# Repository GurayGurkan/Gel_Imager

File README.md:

# Open Science Multi-function Gel Imager
*An Open-Hardware Agorose Gel and Chemiluminicance Imaging System Based on Raspberry Pi 4B*

This repository involves:
  - **Mechanical Design Files**: FreeCAD drawingshousing of Incu-stream mechanical parts
  - **Electronics**: Circuit schematics and PCB layout files of Raspberrry Pi 4B shield and led control electronics.
  - **Software**: Involves Python codes for main control and user interface. 
  -

For suggestions and questions, please e-mail to ***guraygurkan@istanbul.edu.tr***

Cheers!

Guray Gurkan

* **Please cite this repo as:** 

(Under Review: submitted to Scientific Reports for review)

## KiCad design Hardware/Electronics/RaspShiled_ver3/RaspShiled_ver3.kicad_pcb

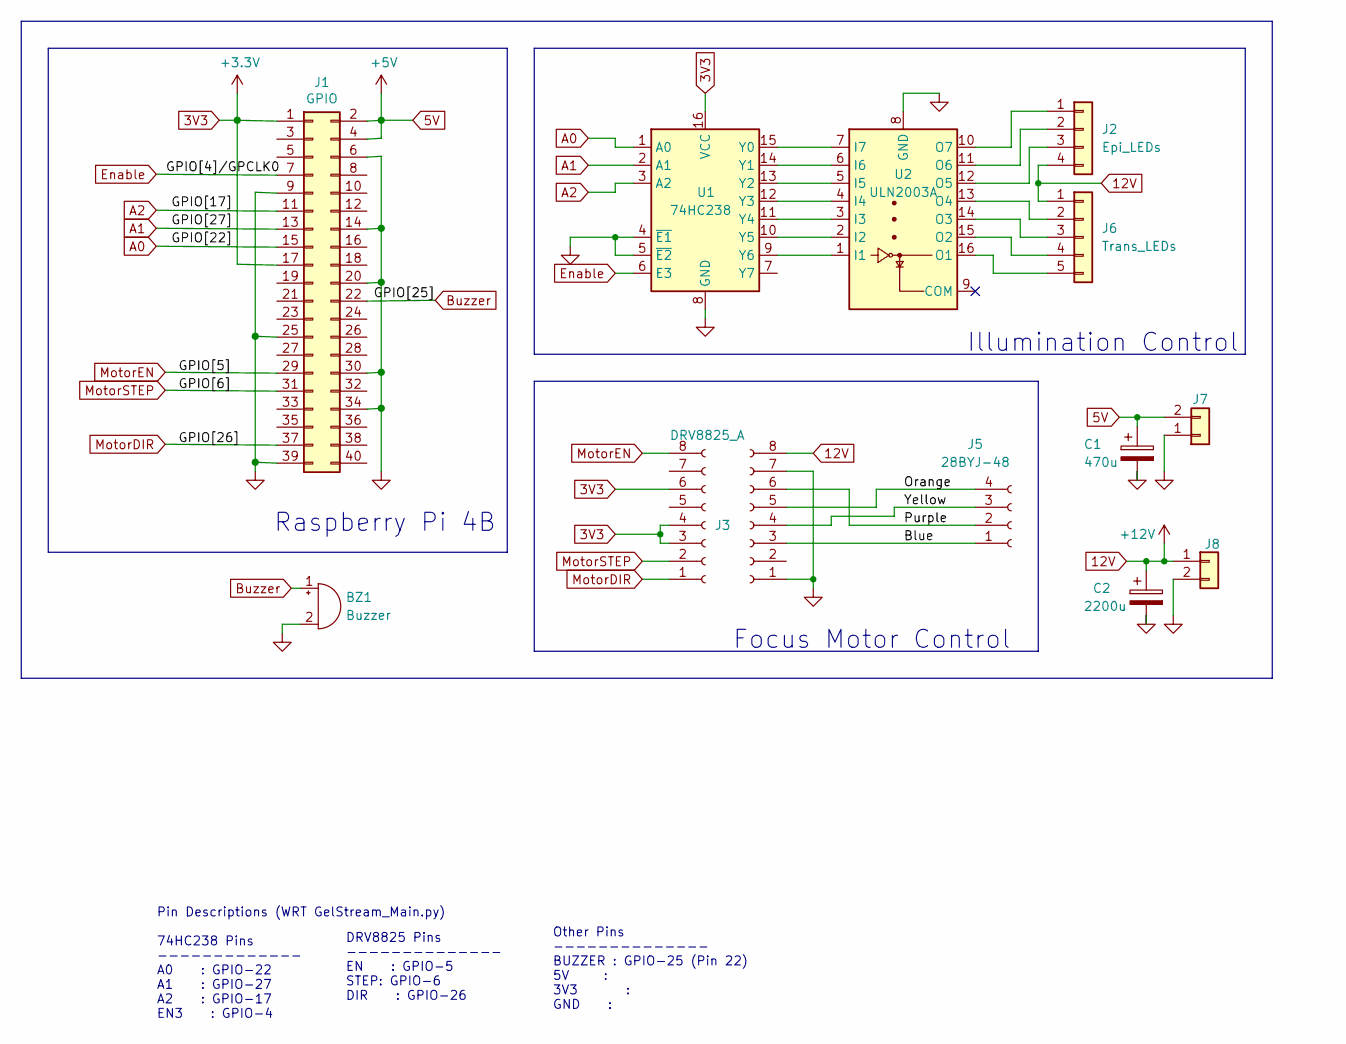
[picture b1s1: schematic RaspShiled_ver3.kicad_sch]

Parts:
BZ1: Buzzer; Buzzer_12x9.5RM7.6
C1: 470u; CP_Radial_D6.3mm_P2.50mm
C2: 2200u; CP_Radial_D6.3mm_P2.50mm
J1: GPIO; PinHeader_2x20_P2.54mm_Vertical
J2: Epi_LEDs; PinHeader_1x04_P2.54mm_Vertical
J3: DRV8825_A; PinSocket_1x08_P2.54mm_Vertical
J4: DRV8825_B; PinSocket_1x08_P2.54mm_Vertical
J5: 28BYJ-48; PinHeader_1x05_P2.54mm_Vertical
J6: Trans_LEDs; PinHeader_1x05_P2.54mm_Vertical
J7, J8: Conn_01x02; TerminalBlock_MetzConnect_Type011_RT05502HBWC_1x02_P5.00mm_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
U1: 74HC238; SOIC-16_3.9x9.9mm_P1.27mm
U2: ULN2003A; DIP-16_W7.62mm

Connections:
3V3: J1.1, J1.17, J3.3, J3.4, J3.6, U1.16 (VCC)
5V: C1.1, J1.2, J1.4, J7.2
12V: C2.1, J2.4, J4.8, J6.1, J8.1
/Blue: J4.3, J5.1
/GPIO[2]/SDA1: J1.3
/GPIO[3]/SCL1: J1.5
/GPIO[7]/SPI0.CE1: J1.26
/GPIO[8]/SPI0.CE0: J1.24
/GPIO[9]/SPI0.MISO: J1.21
/GPIO[10]/SPI0.MOSI: J1.19
/GPIO[11]/SPI0.SCLK: J1.23
/GPIO[12]/PWM0: J1.32
/GPIO[13]/PWM1: J1.33
/GPIO[14]/TXD0: J1.8
/GPIO[15]/RXD0: J1.10
/GPIO[16]: J1.36
/GPIO[18]/PCM.CLK: J1.12
/GPIO[19]/PCM.FS: J1.35
/GPIO[20]/PCM.DIN: J1.38
/GPIO[21]/PCM.DOUT: J1.40
/GPIO[23]: J1.16
/ID_SCL: J1.28
/ID_SDA: J1.27
/Orange: J4.5, J5.4
/Purple: J4.6, J5.2
/Yellow: J4.4, J5.3
A0: J1.15, U1.1 (A0)
A1: J1.13, U1.2 (A1)
A2: J1.11, U1.3 (A2)
Buzzer: BZ1.1 (-), J1.22
Enable: J1.7, U1.6 (E3)
Epi_Blue_EN: U1.15 (Y0), U2.7 (I7)
Epi_Green_EN: U1.13 (Y2), U2.5 (I5)
Epi_Red_EN: U1.14 (Y1), U2.6 (I6)
GND: BZ1.2 (+), C1.2, C2.2, J1.6, J1.9, J1.14, J1.20, J1.25, J1.30, J1.34, J1.39, J4.1, J4.7, J7.1, J8.2, U1.4 (~E1), U1.5 (~E2), U1.8 (GND), U2.8 (GND)
MotorDIR: J1.37, J3.1
MotorEN: J1.29, J3.8
MotorSTEP: J1.31, J3.2
unnamed: J2.1, U2.10 (O7)
unnamed: J2.2, U2.11 (O6)
unnamed: J2.3, U2.12 (O5)
unnamed: J6.2, U2.13 (O4)
unnamed: J6.3, U2.14 (O3)
unnamed: J6.4, U2.15 (O2)
unnamed: J6.5, U2.16 (O1)
Trans_Blue_EN: U1.12 (Y3), U2.4 (I4)
Trans_Green_EN: U1.10 (Y5), U2.2 (I2)
Trans_Red_EN: U1.11 (Y4), U2.3 (I3)
Trans_UV_EN: U1.9 (Y6), U2.1 (I1)

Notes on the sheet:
DRV8825 Pins -------------- EN : GPIO-5 STEP: GPIO-6 DIR : GPIO-26
Illumination Control
Raspberry Pi 4B
Other Pins -------------- BUZZER : GPIO-25 (Pin 22) 5V : 3V3 : GND :
Focus Motor Control
Pin Descriptions (WRT GelStream_Main.py) 74HC238 Pins ------------- A0 : GPIO-22 A1 : GPIO-27 A2 : GPIO-17 EN3 : GPIO-4

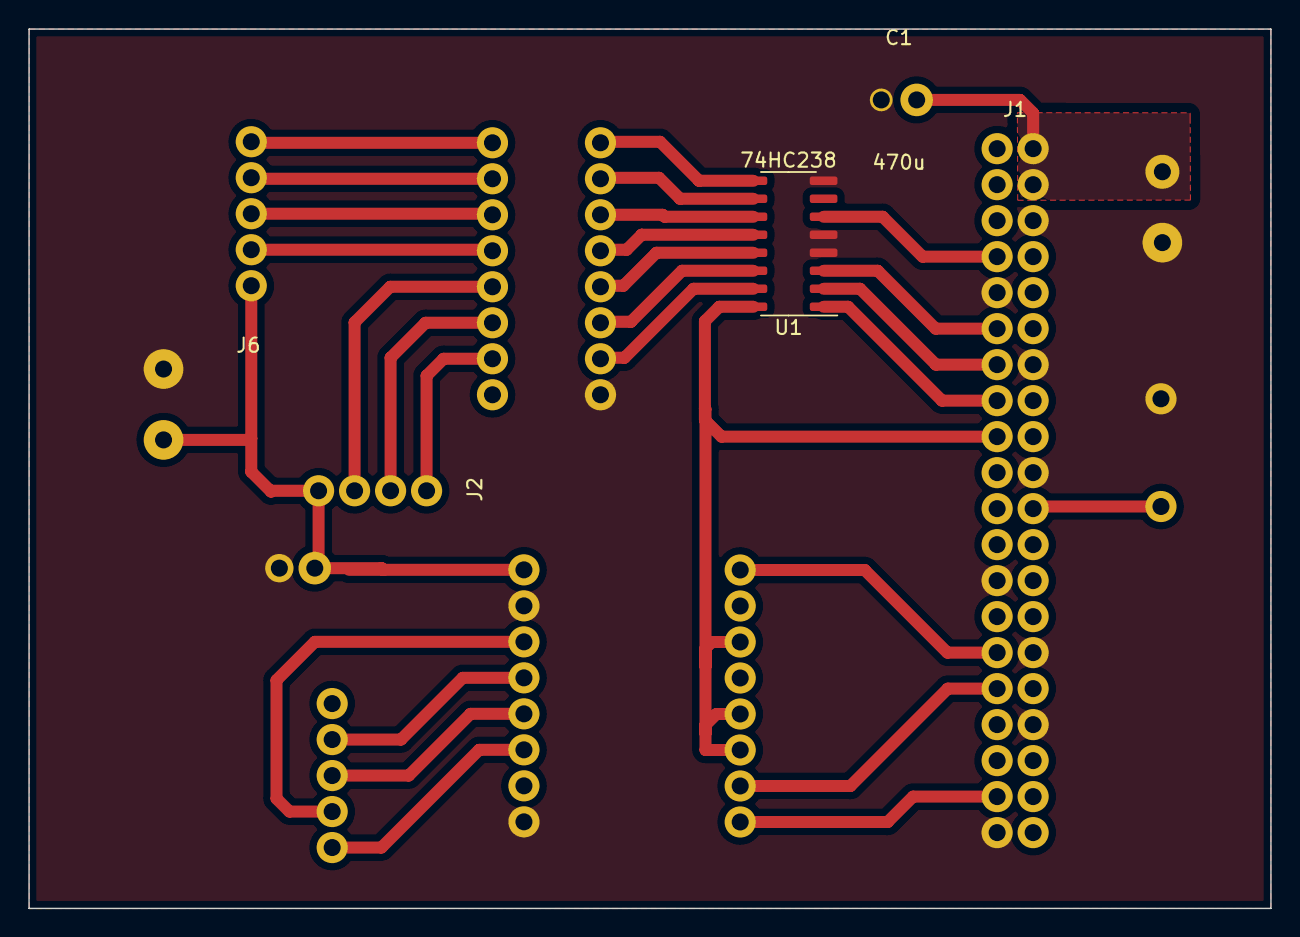
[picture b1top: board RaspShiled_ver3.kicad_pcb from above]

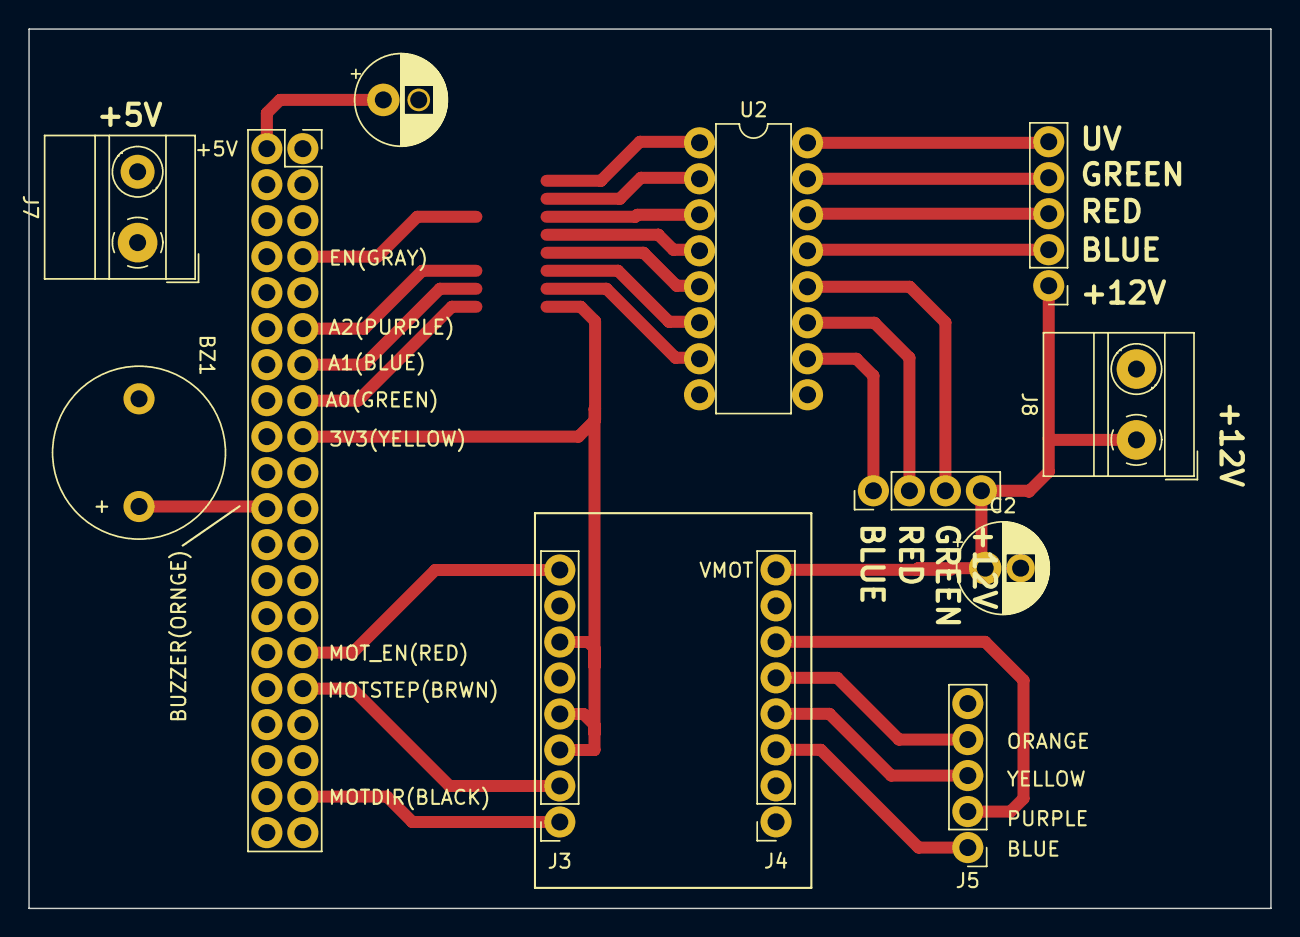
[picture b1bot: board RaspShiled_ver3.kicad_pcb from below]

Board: 2 copper layers, 87.6 x 62.0 mm, 13 parts (12 on the bottom side), 30 nets.

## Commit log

2025-09-10 First Upload
    Primitive Design and Software files for Open-Science Gel Imager Realization
